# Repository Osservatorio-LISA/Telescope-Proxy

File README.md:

# Telescope proxy
This repository contains the code for the LX200GPS ACF AutoStarII telescope command proxy. It's purpose is to interface an ESP32 DevKit V1 with the serial port of the telescope, and provide it as an HTTP resource. Attached is the official LX200 command set protocol released by the manifacturer. The entire structure of this firmware is prototyped in serial_config.h.
## Global Variables
Every time the micro queries the telescope for its position they update the global variables with the current coordinates of the telescope.
There is currentRA, currentDA that store the current DA and RA and is updated every time the position is queried to the telescope. The targetRA and DA instead are used by the set functions to "remember" what position the telescope should reach.
## LX200 functions
These functions act as a interface with the HardwareSerial library to manage the UART interface. These functions all depend on lx200_send_and_recieve_CMD to do their bidding and use the #defines to get the correct command string. The commands used are highlighted on the lx200 command set document. There is an infinity of commands to be implemented but its outside of the scope of this project. 
## Callback functions
These functions manage the requests incoming from the HTTP interface and call the respective LX200 function, parsing strings and checking responses.
## Resources Provided
This version of the firmware provides very basic functions to get the current coordinates of the telescope and set target coordinates and start the slewing. Information gets returned as a JSON via a TCP socket with the keys defined in JSON_key_names.
## info.md
This file is a dump of commands and them getting tested on a terminal connected directly from the machine to the RS232 port of the telescope. It can be useful since the document isnt really accurate on the responses the telescope gives out. 
# REST API TREE
/lx200/ 
    /network/
        /tcp-socket/    -> PUT:  sets tcp-server socket config (ip , port),
                                 ip is necessary, port is 7000 by default
                                 set this params via query (not 100% REST but saves ram. Might change it later.)
                        -> GET:  get current tcp socket
    /settings/
        /resetESP/  -> PUT: reset esp
        /resetLX/   -> PUT: send :I# to the telescope
        /heartbeat/ -> GET: "quick connectivity check"
    /position/      -> GET: get both coordinates
                    -> PUT: set both coords and go: position?RA=DD:MM:SS&DA=sDD:MM:SS
        /RA/        -> GET: get the RA coord string
                    -> PUT: set RA with a query and go: RA?RA=DD:MM:SS
        /DA/        -> GET: get DA coord string
                    -> PUT: set DA with a query and go: DA?DA=sDD:MM:SS, dont worry about the evil 0xDF char as it is handled
        /home/      -> PUT: not implemented
    /stop/

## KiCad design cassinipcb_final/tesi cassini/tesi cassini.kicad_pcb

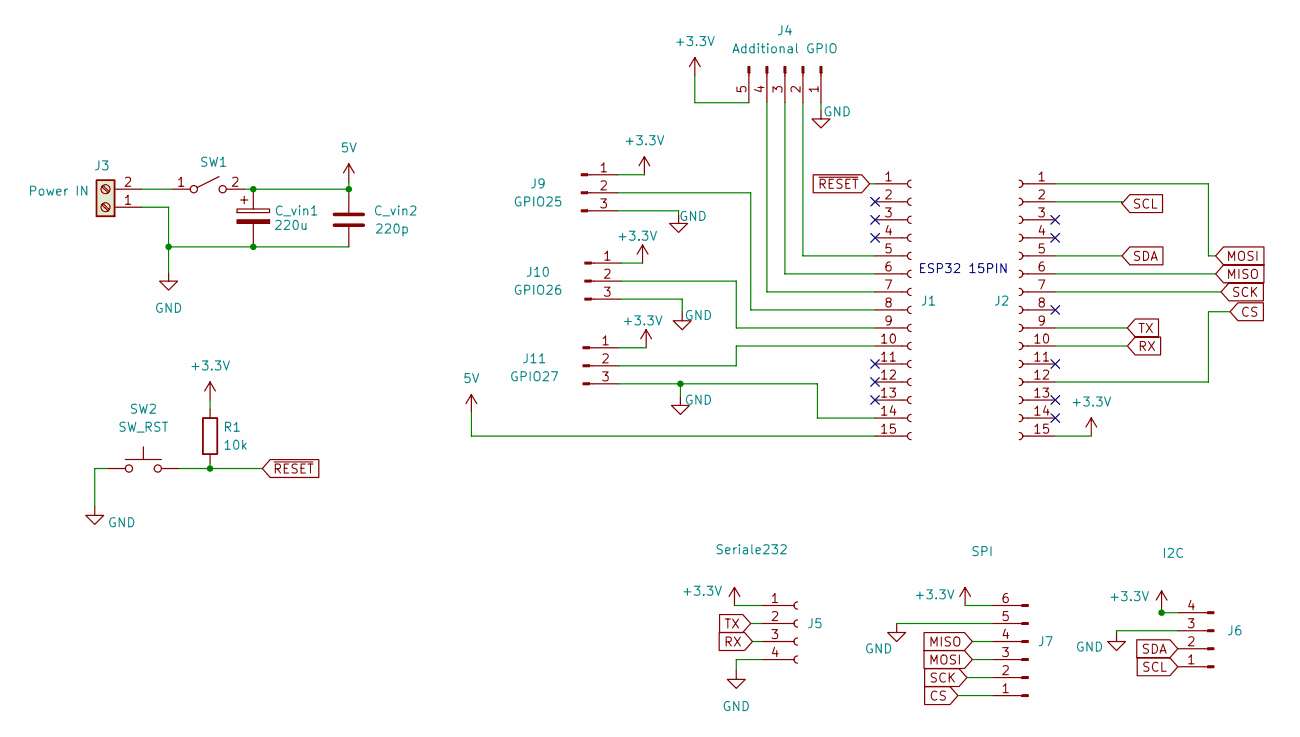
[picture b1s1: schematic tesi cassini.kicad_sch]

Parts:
C_vin1: 220u; CP_Radial_D6.3mm_P2.50mm
C_vin2: 220p; C_Disc_D4.3mm_W1.9mm_P5.00mm
J1, J2: Conn_01x15_Socket; PinSocket_1x15_P2.54mm_Vertical
J3: Power IN; ScrewTerminal2Pin
J4: Additional GPIO; PinHeader_1x05_P2.54mm_Vertical
J5: Seriale232; PinHeader_1x04_P2.54mm_Vertical
J6: I2C; PinHeader_1x04_P2.54mm_Vertical
J7: SPI; PinHeader_1x06_P2.54mm_Vertical
J9: GPIO25; PinHeader_1x03_P2.54mm_Vertical
J10: GPIO26; PinHeader_1x03_P2.54mm_Vertical
J11: GPIO27; PinHeader_1x03_P2.54mm_Vertical
R1: 10k; R_Axial_DIN0204_L3.6mm_D1.6mm_P5.08mm_Horizontal
SW1: SW_SPST; PinHeader_1x02_P2.54mm_Vertical
SW2: SW_RST; PinHeader_1x02_P2.54mm_Vertical

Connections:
5V: C_vin1.1, C_vin2.2, J1.15, SW1.2 (B)
+3.3V: J2.15, J4.5, J5.1, J6.4, J7.6, J9.1, J10.1, J11.1, R1.1
CS: J2.12, J7.1
GND: C_vin1.2, C_vin2.1, J1.14, J3.1, J4.1, J5.4, J6.3, J7.5, J9.3, J10.3, J11.3, SW2.1
MISO: J2.6, J7.4
MOSI: J2.1, J7.3
unnamed: J1.5, J4.2
unnamed: J1.6, J4.3
unnamed: J1.7, J4.4
unnamed: J1.8, J9.2
unnamed: J1.9, J10.2
unnamed: J1.10, J11.2
unnamed: J3.2, SW1.1 (A)
RX: J2.10, J5.3
SCK: J2.7, J7.2
SCL: J2.2, J6.1
SDA: J2.5, J6.2
TX: J2.9, J5.2
~RESET: J1.1, R1.2, SW2.2

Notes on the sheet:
ESP32 15PIN

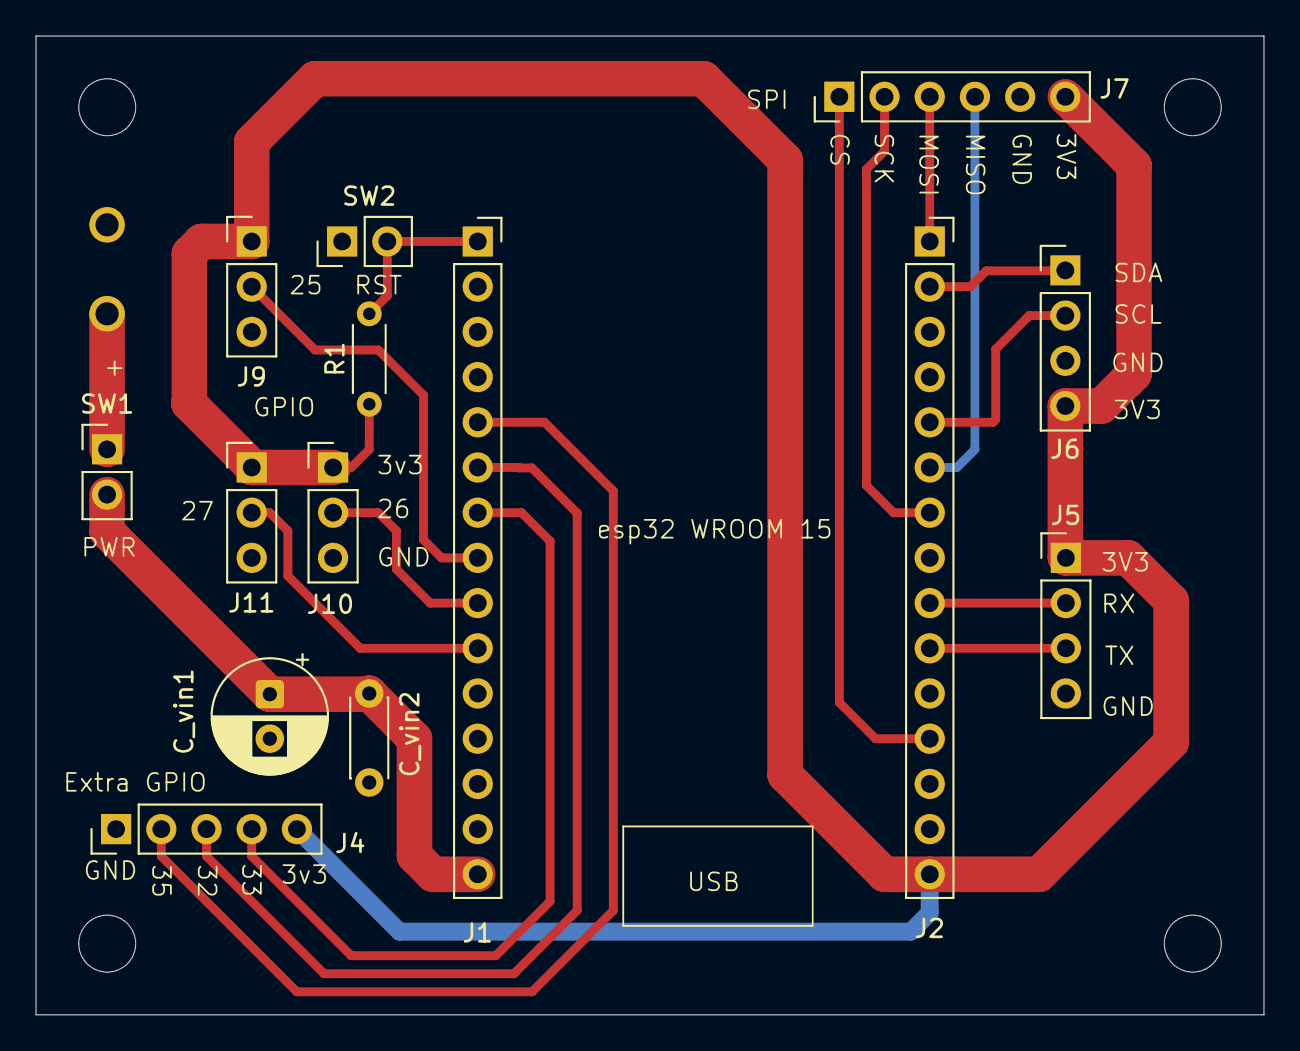
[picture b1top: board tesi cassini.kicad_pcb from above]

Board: 2 copper layers, 69.0 x 55.0 mm, 15 parts (1 on the bottom side), 19 nets.
